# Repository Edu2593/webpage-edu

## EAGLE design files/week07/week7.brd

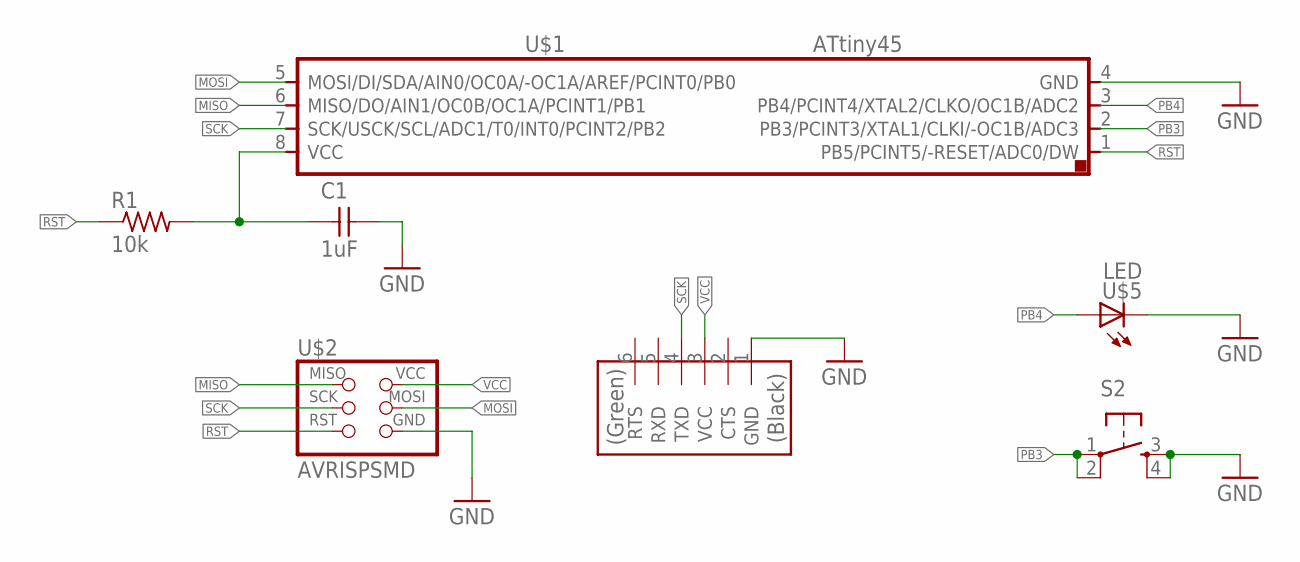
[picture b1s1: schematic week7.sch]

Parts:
C1: 1uF; C1206FAB
R1: 10k; R1206
S2: 6MM_SWITCH6MM_SWITCH; 6MM_SWITCH
U$1: ATTINY45SI; SOIC8
U$2: AVRISPSMD; 2X03SMD
U$3: FTDI-SMD-HEADER; 1X06SMD
U$5: LED; LED1206

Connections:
GND: C1.2, S2.3 (S), S2.4 (S1), U$1.4 (GND), U$2.6 (GND), U$3.1 (GND), U$5.2 (C)
MISO: U$1.6 (MISO/DO/AIN1/OC0B/OC1A/PCINT1/PB1), U$2.1 (MISO)
MOSI: U$1.5 (MOSI/DI/SDA/AIN0/OC0A/-OC1A/AREF/PCINT0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), U$2.4 (MOSI)
unnamed: C1.1, R1.2, U$1.8 (VCC)
PB3: S2.1, S2.2 (P1), U$1.2 (PB3/PCINT3/XTAL1/CLKI/-OC1B/ADC3)
PB4: U$1.3 (PB4/PCINT4/XTAL2/CLKO/OC1B/ADC2), U$5.1 (A)
RST: R1.1, U$1.1 (PB5/PCINT5/-RESET/ADC0/DW), U$2.5 (RST)
SCK: U$1.7 (SCK/USCK/SCL/ADC1/T0/INT0/PCINT2/PB2), U$2.3 (SCK), U$3.4 (TXD)
VCC: U$2.2 (VCC), U$3.3 (VCC)

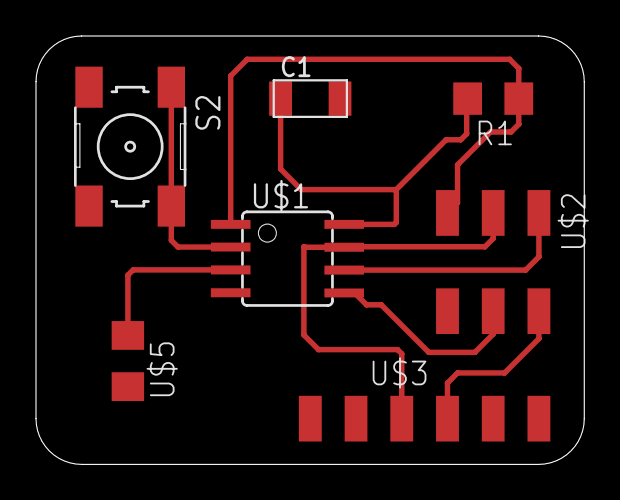
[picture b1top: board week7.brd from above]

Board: 2 copper layers, 30.5 x 23.8 mm, 7 parts (0 on the bottom side), 9 nets.

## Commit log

2019-02-03 Cube
2019-02-03 3.2.2019
2019-02-03 2.3.2019.420
2019-02-03 3.2.2019.428
2019-02-03 3.2.2019.1703
2019-02-03 3.2.2019.1707
2019-02-03 3.2.2019.1712
2019-02-03 3.2.2019.1715
2019-02-03 3.2.2019.1831
2019-02-03 3.2.2019.1846
2019-02-03 3.2.2019.1852
2019-02-04 4.2.2019.0050
2019-02-04 4.2.2019.0054
2019-02-04 4.2.2019.0102
2019-02-04 4.2.2019.0106
2019-02-04 4.2.2019.0802
2019-02-04 04.02.2019.1016
2019-02-04 04.02.2019.1141
2019-02-04 04.02.2019.1204
2019-02-04 0402b
2019-02-04 04.02.2019.1626
2019-02-04 04.02.2019.1639
2019-02-04 04.02.2019.1642
2019-02-04 04.02.2019.1649
2019-02-05 05.02.2019.1637
2019-02-05 05.02.2019.1707
2019-02-06 06.02.2019.0009
2019-02-06 06.02.2019.0140
2019-02-06 06.02.2019.0147
2019-02-06 06.02.2019.0234
2019-02-06 06.02.2019.0257
2019-02-06 06.02.2019.0410
2019-02-06 06.02.2019.0456
2019-02-06 06.02.2019.0505
2019-02-06 06.02.2019.0519
2019-02-12 12.02.2019.1728
2019-02-12 12.02.2019.1741
2019-02-12 12.02.2019.1744
2019-02-19 19.02.2019.1147
2019-02-19 19.02.2019.1341
2019-02-19 19.02.2019.1421
2019-02-20 20.02.2019.0120
2019-02-25 25.02.2019.1246
2019-02-25 25.02.2019.1550
2019-02-27 27.02.2019.0558
2019-02-27 27.02.2019.1217
2019-02-27 27.02.2019.1325
2019-03-02 2.3.2019.0640
2019-03-05 04.03.2019.2018
2019-03-05 05.03.2019.0008
2019-03-06 05.03.2019.2046
2019-03-06 06.03.2019.0203
2019-03-06 06.03.2019.0925
2019-03-07 07.03.2019.1753
2019-03-27 27.03.0608
2019-04-16 16.04.2019.17:35
2019-04-20 20.04.2019.13:06
2019-04-23 23.04.2019.10:51
2019-04-24 23.04.2019.11:34
2019-04-24 24.04.2019.06:35
2019-06-09 10.06.2019.15:47
